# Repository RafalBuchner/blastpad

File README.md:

# BLASTPad Documentation

**BLASTPad** is a macropad – a programmable keyboard with 23 customazible keys and 2 encoders (knobs). 

# Instruction

## Layout

Keyborad's layout was designed to resamble the most left 5 columns of a standard keyborad with the exclusion of the top row (which usually contains all the _F_ keys together with _ESC_ key ). All of the keys are programmable, which means that with the help of a small desktop app you will be able to change behaviour of each key by assigning keystroke combinations to all of them.  Additionally **BLASTPad** has two rotary encoders, which also can trigger some keystroke actions.

## First Run

1. Connect your **BLASTPad** to your computer via USB MICRO B cable. New usb storage device called **BLASTPAD** should appear. We will talk about it more later.
2. Wait until **BLAST** logo will disappear.
3. You should see the similar data on the display:

- "Default" is a title of currently active **Preset**.
- "Numbers" is a title of an **Encoder Action** currently assigned to the **Encoder 1**
- "Up/Down" is a title of an **Encoder Action** currently assigned to the **Encoder 2**

### Encoder Basics

In next the chapter we will talk more about **Presets** and how to set them up together with the **Key and Encoder Actions**.  For now let's focus on the behaviour of the latter.

#### Changing the Encoder Actions:

Push the knob like it were a button.

You can see on the display that encoder changed it's title and therefore it changed its behaviour. Each **Preset** has its own set of "behaviours" that can be assigned to eighter **Encoder 1** or **Encoder 2** (see chapter **Creating and editing Presets** to learn how to create those behaviours).

There are two **types of Encoder Actions**:

- **"Left/Right" Encoder Action**

  >  In this action you have assigned two keystrokes to the encoder: one to the counterclockwise and the other one to the cockwise movements.
  >
  > Good example is the "Up/Down" action. Left movement performs "UP ARROW" keystroke, while right movement performs "DOWN ARROW" keystroke. Test it, for example, in some text editor. You will see that the cursor behaves in a similar way, as you would hit the arrow buttons.

- **"Carousel" Encoder Action**

  >"Numbers" is a good example of a carousel action. In this action when you rotate knob clockwise, it will execute numerical keystroke. With every step the keystroke will represent incremented digit starting from *0* (zero) until it will reach the *9*. After this, the counting will reset to *0*.
  >
  >If you'll rotate know counterclockwise, the operation will work almost the same. Except, this time instead of incrementing, it will decrement digits.

## Creating and editing Presets

**Preset** is a singular set of instructions, which determines what keystroke sequence will be triggered by your keys or encoders. You can store almost as many presets on your **BlastPad** as you want.

#### Maximum number of actions in the Preset:

Each **Preset** has actions assigned to the keys, which max number in the preset is equal to the number of the buttons in **BLASTPad**'s keyboard layout (23 – excluding the special lonely key on the right side of the device). Besides **Key Actions**, each preset can have **Encoder Actions**. Number of those is in theory limitless. You can switch between all of **Preset**'s **Encoder Actions** with just two physical encoders. 

#### BlastPadControl app

### MacOS

>  (Currently alpha pre-release version.)

#### Opening the app

Download the zip file from this site:

https://github.com/RafalBuchner/blastpad/releases/download/v0.0.0.1-alpha/BlastPadControl.macOS.zip

Or go to the main GitHub page of this project (https://github.com/RafalBuchner/blastpad) and look for the link in the download section of the documentation. 

Inside the unzipped folder you will find BlastPadControl executable file. Double click on it. The window like one below should appear:

This is the **Preset** Editor. It is divided into two sections. One is responsible for controling the **Key Actions**. The other one for creating and editing the **Encoder Actions**.

### Key Actions Section

**The Key Actions Section**'s buttons recreates the **BlastPad**'s keyboard layout. If you click on the one of the buttons, the popup window will appear.

In this window you can assign pressed keystroke sequence to the previously selected button on the **Key Action Section**. 

Simply press some keystroke sequence on your everyday-regular-keyboard and press "ok" button (**IMPORTANT**: Pacience, This keystroke won't be triggered by the corresponding key on the **BLASTPad** device yet – we will talk about saving presets onto the device soon).

This way you can edit all of the buttons on the **Key Action Section** layout. It is super easy.

### Encoder Actions Section

**Encoder Actions Section** is a list, where each row represent different **Encoder Actions**. Each column cell (except the one reserved for the name) defines Keystroke/Hotkey.

- To create a new **Encoder Action** hit *"add encoder"* button. It will create a new row. 

- Double click on the cell with the title "new encoder" to set the **Encoder Action**'s name that will appear on the **BLASTPad**'s display.

- Click on one of the hotkey cells to assign keystroke sequence.

### Creating "Left/Right" Encoder Action

To create a **"Left/Right" Encoder Action** you have to assign 2 hotkeys to the encoder. One in the column "hotkey 1" and the otherone in the column "hotkey 2". 

The first one will be triggered when you rotate physical encoder counterclockwise. The second, whenever you rotate the same encoder in clockwise direction.

### Creating "Carousel" Encoder Action

To create a **"Carousel" Encoder Action** you have to assign any number of hotkeys, except 2.

If you want to have additional hotkey slots created, hit *"add hotkey"* button. You can add as many as you want.

### Saving presets onto the device

You save **Presets** as separate files with **.json* extension. 

Press *Save* button to create a **Preset** file. In order to save preset on your **BLASTPad** find the usb device with the same name and save the **Preset** into *"Configs"* folder. The name of the file will be used as a **Preset Title** on the **BlastPad**'s display, so name it accordingly to your needs.

### Changing the active Presets on the BlastPad device.

If you have more than one **Presets** you will be able to swich between the presets whenever you like!

It is super easy. Hold **Action Key** (the lonley key on the right side of the device). You will enter the **Preset Selection** menu. Now, rotate your **Encoder 1** while holding the key. This way you will switch between the **Presets**.

### Windows 

> (It is currently under construction. Beta version is coming very soon.)

# Downloads

## BlastPadControl

### [MacOS Download link](https://github.com/RafalBuchner/blastpad/releases/download/v0.0.0.1-alpha/BlastPadControl.macOS.zip)

## Photos

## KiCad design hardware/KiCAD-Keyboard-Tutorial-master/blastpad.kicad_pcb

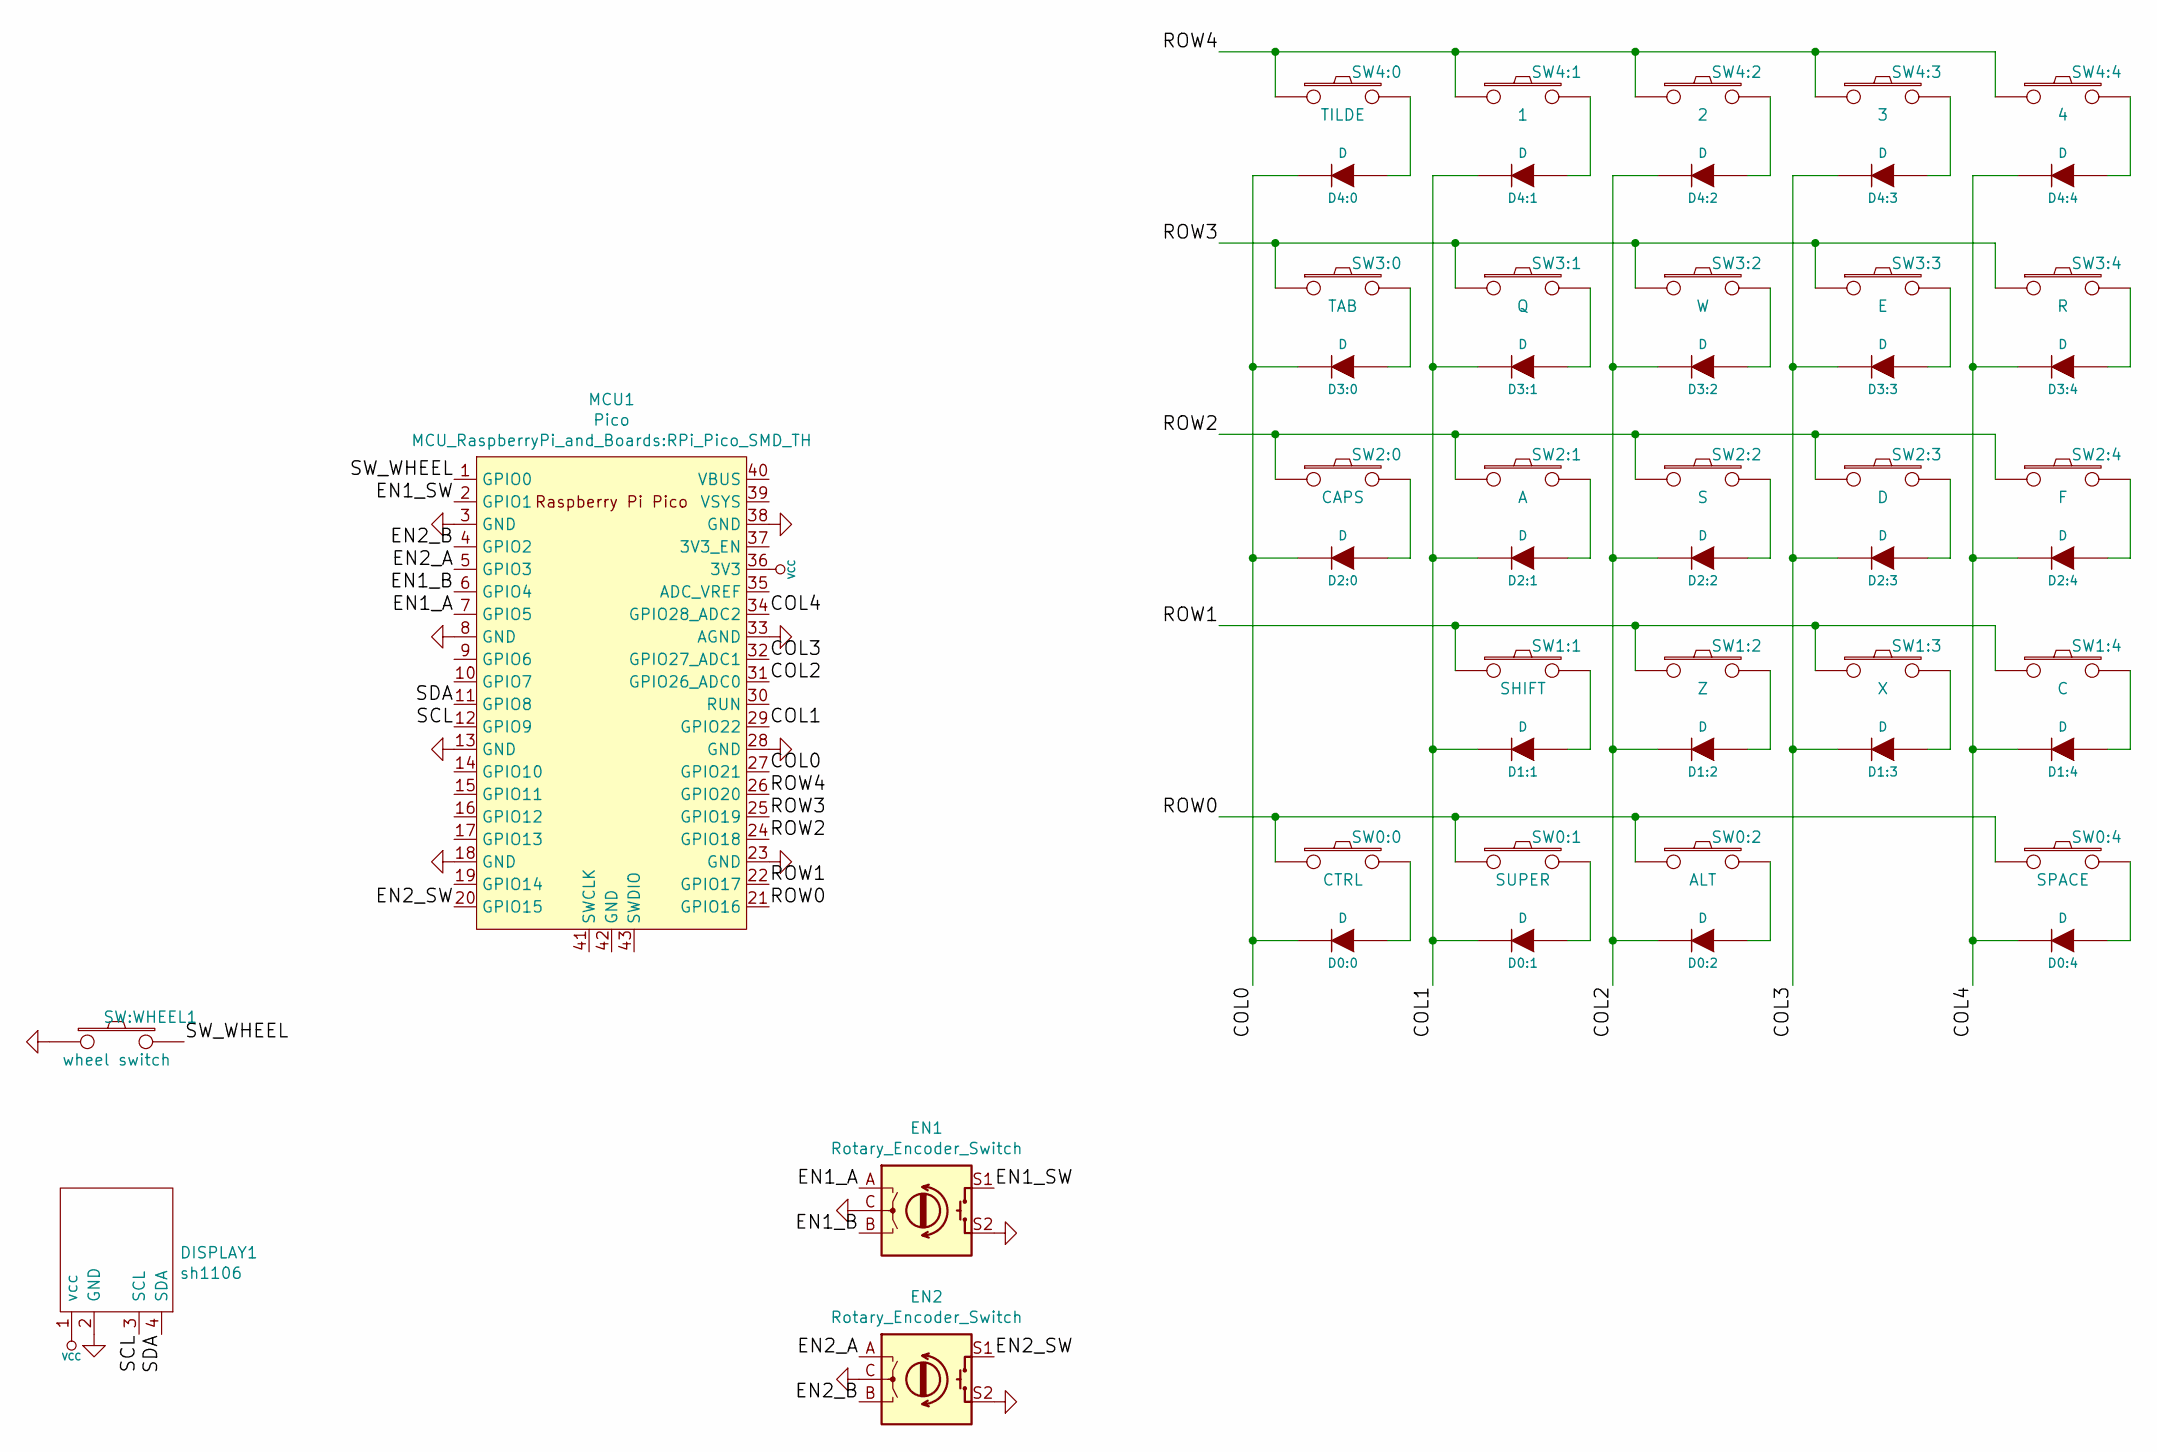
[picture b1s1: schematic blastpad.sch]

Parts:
D0:0, D0:1, D0:2, D0:4, D1:1, D1:2, D1:3, D1:4, D2:0, D2:1, D2:2, D2:3, D2:4, D3:0, D3:1, D3:2, D3:3, D3:4, D4:0, D4:1, D4:2, D4:3, D4:4: D; DIODE
DISPLAY1: sh1106; 4pin oled display 1,3
EN1, EN2: Rotary_Encoder_Switch; RotaryEncoder_Alps_EC12E-Switch_Vertical_H20mm
MCU1: Pico; RPi_Pico_SMD_TH
SW0:0: CTRL; CHERRY_PCB_100H
SW0:1: SUPER; CHERRY_PCB_100H
SW0:2: ALT; CHERRY_PCB_100H
SW0:4: SPACE; CHERRY_PCB_200H
SW1:1: SHIFT; CHERRY_PCB_200H
SW1:2: Z; CHERRY_PCB_100H
SW1:3: X; CHERRY_PCB_100H
SW1:4: C; CHERRY_PCB_100H
SW2:0: CAPS; CHERRY_PCB_100H
SW2:1: A; CHERRY_PCB_100H
SW2:2: S; CHERRY_PCB_100H
SW2:3: D; CHERRY_PCB_100H
SW2:4: F; CHERRY_PCB_100H
SW3:0: TAB; CHERRY_PCB_100H
SW3:1: Q; CHERRY_PCB_100H
SW3:2: W; CHERRY_PCB_100H
SW3:3: E; CHERRY_PCB_100H
SW3:4: R; CHERRY_PCB_100H
SW4:0: TILDE; CHERRY_PCB_100H
SW4:1: 1; CHERRY_PCB_100H
SW4:2: 2; CHERRY_PCB_100H
SW4:3: 3; CHERRY_PCB_100H
SW4:4: 4; CHERRY_PCB_100H
SW:WHEEL1: wheel switch; CHERRY_PCB_100H

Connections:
/COL0: D0:0.2 (K), D2:0.2 (K), D3:0.2 (K), D4:0.2 (K), MCU1.27 (GPIO21)
/COL1: D0:1.2 (K), D1:1.2 (K), D2:1.2 (K), D3:1.2 (K), D4:1.2 (K), MCU1.29 (GPIO22)
/COL2: D0:2.2 (K), D1:2.2 (K), D2:2.2 (K), D3:2.2 (K), D4:2.2 (K), MCU1.31 (GPIO26_ADC0)
/COL3: D1:3.2 (K), D2:3.2 (K), D3:3.2 (K), D4:3.2 (K), MCU1.32 (GPIO27_ADC1)
/COL4: D0:4.2 (K), D1:4.2 (K), D2:4.2 (K), D3:4.2 (K), D4:4.2 (K), MCU1.34 (GPIO28_ADC2)
/EN1_A: EN1.A, MCU1.7 (GPIO5)
/EN1_B: EN1.B, MCU1.6 (GPIO4)
/EN1_SW: EN1.S1, MCU1.2 (GPIO1)
/EN2_A: EN2.A, MCU1.5 (GPIO3)
/EN2_B: EN2.B, MCU1.4 (GPIO2)
/EN2_SW: EN2.S1, MCU1.20 (GPIO15)
/ROW0: MCU1.21 (GPIO16), SW0:0.1, SW0:1.1, SW0:2.1, SW0:4.1
/ROW1: MCU1.22 (GPIO17), SW1:1.1, SW1:2.1, SW1:3.1, SW1:4.1
/ROW2: MCU1.24 (GPIO18), SW2:0.1, SW2:1.1, SW2:2.1, SW2:3.1, SW2:4.1
/ROW3: MCU1.25 (GPIO19), SW3:0.1, SW3:1.1, SW3:2.1, SW3:3.1, SW3:4.1
/ROW4: MCU1.26 (GPIO20), SW4:0.1, SW4:1.1, SW4:2.1, SW4:3.1, SW4:4.1
/SCL: DISPLAY1.3 (SCL), MCU1.12 (GPIO9)
/SDA: DISPLAY1.4 (SDA), MCU1.11 (GPIO8)
/SW_WHEEL: MCU1.1 (GPIO0), SW:WHEEL1.2
GND: DISPLAY1.2 (GND), EN1.C, EN1.S2, EN2.C, EN2.S2, MCU1.3 (GND), MCU1.8 (GND), MCU1.13 (GND), MCU1.18 (GND), MCU1.23 (GND), MCU1.28 (GND), MCU1.33 (AGND), MCU1.38 (GND), SW:WHEEL1.1
unnamed: D0:0.1 (A), SW0:0.2
unnamed: D0:1.1 (A), SW0:1.2
unnamed: D0:2.1 (A), SW0:2.2
unnamed: D0:4.1 (A), SW0:4.2
unnamed: D1:1.1 (A), SW1:1.2
unnamed: D1:2.1 (A), SW1:2.2
unnamed: D1:3.1 (A), SW1:3.2
unnamed: D1:4.1 (A), SW1:4.2
unnamed: D2:0.1 (A), SW2:0.2
unnamed: D2:1.1 (A), SW2:1.2
unnamed: D2:2.1 (A), SW2:2.2
unnamed: D2:3.1 (A), SW2:3.2
unnamed: D2:4.1 (A), SW2:4.2
unnamed: D3:0.1 (A), SW3:0.2
unnamed: D3:1.1 (A), SW3:1.2
unnamed: D3:2.1 (A), SW3:2.2
unnamed: D3:3.1 (A), SW3:3.2
unnamed: D3:4.1 (A), SW3:4.2
unnamed: D4:0.1 (A), SW4:0.2
unnamed: D4:1.1 (A), SW4:1.2
unnamed: D4:2.1 (A), SW4:2.2
unnamed: D4:3.1 (A), SW4:3.2
unnamed: D4:4.1 (A), SW4:4.2
VCC: DISPLAY1.1 (vcc), MCU1.36 (3V3)

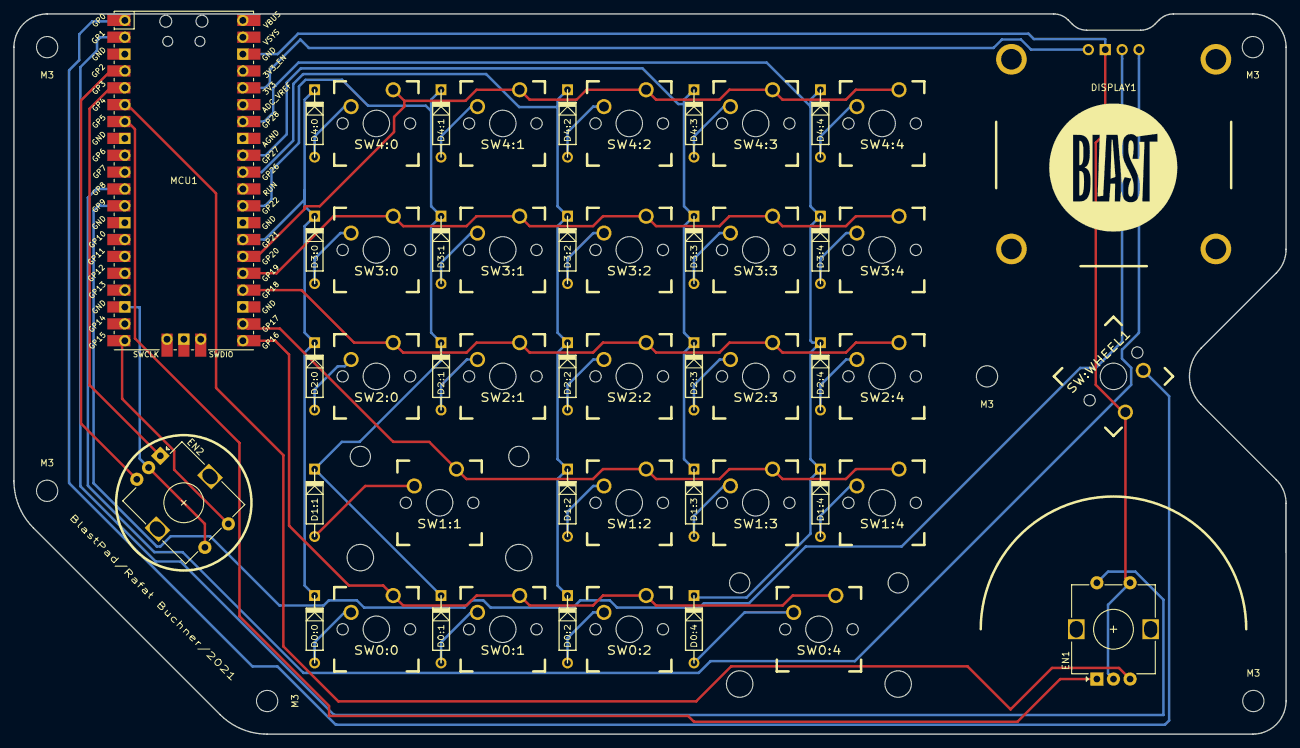
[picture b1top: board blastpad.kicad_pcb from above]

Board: 2 copper layers, 191.7 x 108.5 mm, 57 parts (0 on the bottom side), 44 nets.

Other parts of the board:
M3, M3#2, M3#3, M3#4, M3#5, M3#6: MountingHole_3.2mm_M3

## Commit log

2021-10-12 gitignore update
2021-10-12 hardwareUpdate
2021-10-12 name change
2021-10-13 pcb designed 1
2021-10-16 pcb polished
2021-10-16 hardware name change to blastpad
2021-11-22 backup update
2021-11-26 huge update
2021-12-23 package cover
2022-02-05 documentation
2022-02-05 huge
